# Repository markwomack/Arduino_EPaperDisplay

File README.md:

# Arduino EPaperDisplay Example
## Introduction
Arduino code to drive a Waveshare e-Paper display and example to demonstrate usage.

This code is written specifically for this e-Paper display model from Waveshare:

[2.13" Touch e-Paper HAT for Raspberry Pi, 250×122, Black / White, SPI](https://www.waveshare.com/product/displays/e-paper/epaper-3/2.13inch-touch-e-paper-hat.htm)

While this display is meant for use with a Raspberry Pi, it is still
compatible with Arduino. And in fact, Waveshare has Arduino example code to drive
the display (but not the touch screen) located here:

[epd2in13_V3](https://github.com/waveshare/e-Paper/tree/master/Arduino/epd2in13_V3)

I started with that Waveshare code to create my code. Much of the structure
and code is the same, just cleaned up with better class organization and added
features. I don't have any documentation about the SPI commands, so I have just copied
them over as-is. I will add more comments and documentation as I learn more.

## Licenses
All of this code is released under the MIT license except where noted in any files. The
original Waveshare code that was heavily used as a working example for this code had
it's own permissive license, which is noted in the file LICENSE-Waveshare. The fonts
used in this demo come from STMicroelectronics, and were originally included in the
Waveshare demo code. They have their own permissive license included in those files.

## Usage

### EPaperDisplay
EPaperDisplay is the class that defines the features and functions of the display. You will
typically create an instance at the start of the program, configure it for usage, and then
start the display for rendering.

#### Configuration
There are two main methods used to configure the display before usage. Typically you will
call these methods once before calling the start method.

- **setPinsAndSPI** - This method is called to configure the physical pins that the display
is connected to on the microcontroller (Arduino). The display uses the SPI protocol to
receive commands and data. The connections on the physical display are made either to
the solder points on the display or through the 40 pin Raspberry Pi header. The Pi
connections are documented in the picture below.

- **setDisplayOrientation** - This method sets the orientation of the display, effectively
where the origin of the screen is when rendering. Once the display has been started, the
orientation cannot be changed. The default orientation is ROTATE_0, so if that matches
your usage, then no call is necessary. The picture below shows the origins of each
orientation.

#### Using the Display

- **start** - The start method is called to initialize the display for usage. It returns a
PaintBuffer instance, which is used to render pixels, lines, rectangles, circles, fonts,
and bitmaps into the buffer for the display. More information on the
[PaintBuffer class](#paintbuffer) is below.
By default the display is created with an underlying buffer that is the full size of the
screen (FULL_BUFFER). For a black and white image at 122 x 250 pixels this is 4000 bytes.
If that is too much for your available runtime memory, you can pass the value
PARTIAL_BUFFER as a parameter to the start method and a smaller buffer will be created.
However, this has implications for rendering, which is discussed further in the [Demo Code
section](#demo-code) below. Typically you only need to call this method once, at the start
of the program, using a full size buffer.
- **stop** - The stop method is called to stop the display and release all of the memory
associated with it, this includes the underlying buffer and the associated PaintBuffer
object. After calling stop, the PaintBuffer instance returned from the call to the start
method should be discarded (it's already been freed in stop). Typically the stop method
is never called, but if there is a project that requires it, the display can be restarted
once again by another call to the start method.
- **setMode** - The setMode method must be called before the refresh method is called. It
'wakes' the display up from sleep mode and readys the display to receive data.
- **refresh** - The refresh method is used to render the current contents of the underlying
buffer to the display. If using a full size buffer (FULL_BUFFER), refresh only
needs to be called once to render the buffer to the display. If a partial buffer is used,
then 5 calls to refresh are required to render a full size buffer to the display. This is
discussed more in the [Demo Code section](#demo-code) below.
- **sleep** - After updating the display with the image data, you can call the sleep method
to place the display into low power sleep mode. In this mode the display will draw a 
very small amount of current, but the current image on the display will be maintained.
Once in sleep mode, use the setMode method to 'wake up' the display for rendering.
- **reset** - The reset method will perform a hardware reset of the display. This can be
used if the display becomes unresponsive.
- **getWidth** - This method returns the width of the display based on the current display
orientation. If the orientation is ROTATE_0 or ROTATE_180, the width will be 122, and
if the orientation is ROTATE_90 or ROTATE_270, the width will be 250.
- **getHeight** - This method returns the height of the display based on the current display
orientation. If the orientation is ROTATE_0 or ROTATE_180, the height will be 250, and
if the orientation is ROTATE_90 or ROTATE_270, the height will be 122.

#### Memory usage
The underlying buffer and PaintBuffer object are allocated with the call to the start method
and deallocated with the call to stop method. Typical usage has just the call to the start
method, so memory is not constantly allocated and deallocated. As mentioned above, by default
the EPaperDisplay class will allocated a buffer to match the full size of the display, which
is 122 x 250 black or white pixesl. It works out to 4000 bytes for the buffer.

### PaintBuffer
The PaintBuffer class has basic primitives to render points, lines, rectangles, circles, 
strings, and bitmaps. It uses the same underlying buffer created by the EPaperDisplay instance,
so memory is conserved. You get a reference to the paint buffer by calling the start method
of the display.

- **eraseBuffer** - Use eraseBuffer to clear the entire buffer to the given color. By default
this color is WHITE, but you can pass in BLACK as the value to set the entire buffer to black.
- **setColor** - Use the setColor method to set the color that elements will be drawn in. By
default this color is BLACK, but you can set the color to WHITE if drawing on a black
background. You can draw in inverse (BLACK background, WHITE drawings), then use the
eraseBuffer(BLACK) to fill the entire buffer with black, and use setColor(WHITE)
to change the drawing color, and render your desired objects.
- **getColor** - Returns the current color set in the PaintBuffer.
- **drawPixel** - Draws a pixel at the given point, in the current color.
- **drawLine** - Draws a line between two given points, in the current color.
- **drawRectangle** - Draws a rectangle between two given points, in the current color.
- **drawFilledRectangle** - Draws a filled rectangle between to given points, in the current
color.
- **drawCircle** - Draws a circle centered on a given point with the given radious, in the
current color.
- **drawFilledCircle** - Draws a filledcircle centered on a given point with the given radious,
in the current color.
- **drawBitmap** - Draws a bitmap, located in normal memory, of a given width and height with
the top left of the bitmap starting at a given point. Be default only the bits in the image
that are set will be rendered in the current color (skipUnsetBits = true). But if skipUnsetBits
parameter is set to false, then the set bits are rendered in the current color and the unset
bits are rendered in the opposite color.
- **drawBitmapFromProgMem** - Draws a bitmap, located in PROG_MEM, of a given width and height
with the top left of the bitmap starting at a given point. Be default only the bits in the image
that are set will be rendered in the current color (skipUnsetBits = true). But if skipUnsetBits
parameter is set to false, then the set bits are rendered in the current color and the unset
bits are rendered in the opposite color.
- **drawStringAt** - Draws a given string, using one of the built-in fonts located in PROG_MEM,
justified around a given point. If LEFT_JUSTIFIED, the default, the top/left of the string
will start at the given point. If CENTER_JUSTIFIED, the string will render to the left of the
point with the point being at the center/top of the rendered string. If RIGHT_JUSTIFIED, the
top/right of the string will end at the given point.
- **getWidth** - This method returns the width of the display based on the current display
orientation and buffer type. If the buffer type is FULL_BUFFER and the orientation is
ROTATE_0 or ROTATE_180, the width will be 122, and if the orientation is ROTATE_90 or
ROTATE_270, the width will be 250. If the buffer type is PARTIAL_BUFFER, then the buffer
is smaller, only 1/5th the size. If the orientation is ROTATE_0 or ROTATE_180, the width will
be 122, and if the orientation is ROTATE_90 or ROTATE_270, the width will be 50.
- **getHeight**- This method returns the height of the display based on the current display
orientation and buffer type. If the buffer type is FULL_BUFFER and the orientation is
ROTATE_0 or ROTATE_180, the height will be 250, and if the orientation is ROTATE_90 or
ROTATE_270, the height will be 122. If the buffer type is PARTIAL_BUFFER, then the buffer
is smaller, only 1/5th the size. If the orientation is ROTATE_0 or ROTATE_180, the width will
be 50, and if the orientation is ROTATE_90 or ROTATE_270, the width will be 122.
- **useOffsetStep** - If using a PARTIAL_BUFFER, and you still want the drawing to be rendered
as if there is a full buffer, then set this value to true (the default is false). You will need
to draw the full image multiple times, and this is discussed further in the
[Demo Code section](#demo-code) below.
- **setOffsetStep** - Do not use this method. It is called by the parent EParentDisplay to
coordinate with the PaintBuffer when refreshing with a partial buffer.

#### Image Basics
If you are creating your own images to be displayed, please keep in mind some of these basic
facts. A single image byte represents 8 pixels, one bit for each pixel, with the most significant
bit being the leftmost pixel. As an example, an image that is 24 pixels wide and 24 pixels in
height, each row of the image will be 3 bytes wide, and there will be 24 rows. The total number
of bytes will be 3 x 24 = 72. But what if the width of the image is not a multiple of 8? If we
have an image that is 21 pixels wide and 21 pixels in height, how many bytes should each row be?
2 bytes is not enough bits (16 bits) and 3 bytes is more than is needed (24 bits).

In cases where the pixel width is not a multiple of 8, we round up the number of bytes. In this
case: 3 bytes. The extra bits are just ignored. But they are still accounted for in the memory
allocated for the image. An image 24 x 24 pixels and an image that is 21 x 24 pixels require the
same amount of memory, 72 bytes.

The formula to use when determining the 'byte' width of an image is:

```
if (pixelWidth % 8 == 0) { 
  byteWidth = pixelWidth / 8;       // pixel width is a multiple of 8
} else {
  byteWidth = (pixelWidth / 8) + 1; // pixel width is not a multiple of 8, add a byte for padding
}
```

## Demo Code
The demo code in the Arduino_EPaperDisplay.ino sketch demonstrates usage for almost all of the
methods outlined.

### fullBufferDemo
This method renders a number of screens that are shown in the display when
the image buffer matches the full size of the display. It demonstrates use of all the shape,
string, and bitmap methods, using different colors and different display orientations. Normal
usage will probably not require multiple calls to the start and stop methods, but changing
orientation in the demo requires it.

### partialBufferDemo
This method demonstrates the usage of the EPaperDisplay and PaintBuffer
objects when only a partial buffer is allocated. When PARTIAL_BUFFER is given as a parameter to
the start method, a buffer that is only 1/5th the size of the full display is allocated. The
size of the buffer in pixels is only 122 x 50. Using a partial buffer changes the behavior of the
refresh method. Where the display was updated with just one call to refresh, the display will not
update until there have been 5 calls to refresh, each call updating a segment of the display. All
of the updates won't be displayed until the fifth call.

The first two examples show how this works when the display orientation is the default ROTATE_0.
Each segment is rendered independent of each other, working progressively down the 250 pixel height
of the display. This might be useful, but not likely. The situation gets even worse when the
display orientation is changed, as the third example shows. The text is rotation and displayed
in each segment. The issue is that drawing in the PaintBuffer is being done in the buffer coordinates,
not the display coordinates.

But in order for the display coordinates to make sense across all 5 buffer segments, you will need
to call the useOffsetStep method. This configures the PaintBuffer to work with the parent
EPaperDisplay object to count the number of refresh calls and to offset the coordinates accordingly.
But in order for this to work you will need to draw the same buffer contents each of the 5 calls to
refresh. It is a lot of duplication, but it works perfectly. All of the following examples demonstrate
this by drawing the same buffer 5 times using display coordinates instead of buffer coordinates. This
technique works with all display orientations and all of the paint buffer drawing methods. Pixels that
would be rendered outside of the mapped buffer are ignored so that memory is not corrupted.

## Questions, Concerns, Bugs
If you have any questions or encounter bugs, [please report a new issue](https://github.com/markwomack/Arduino_EPaperDisplay/issues).
Please provide as much detail and sample code that you can.

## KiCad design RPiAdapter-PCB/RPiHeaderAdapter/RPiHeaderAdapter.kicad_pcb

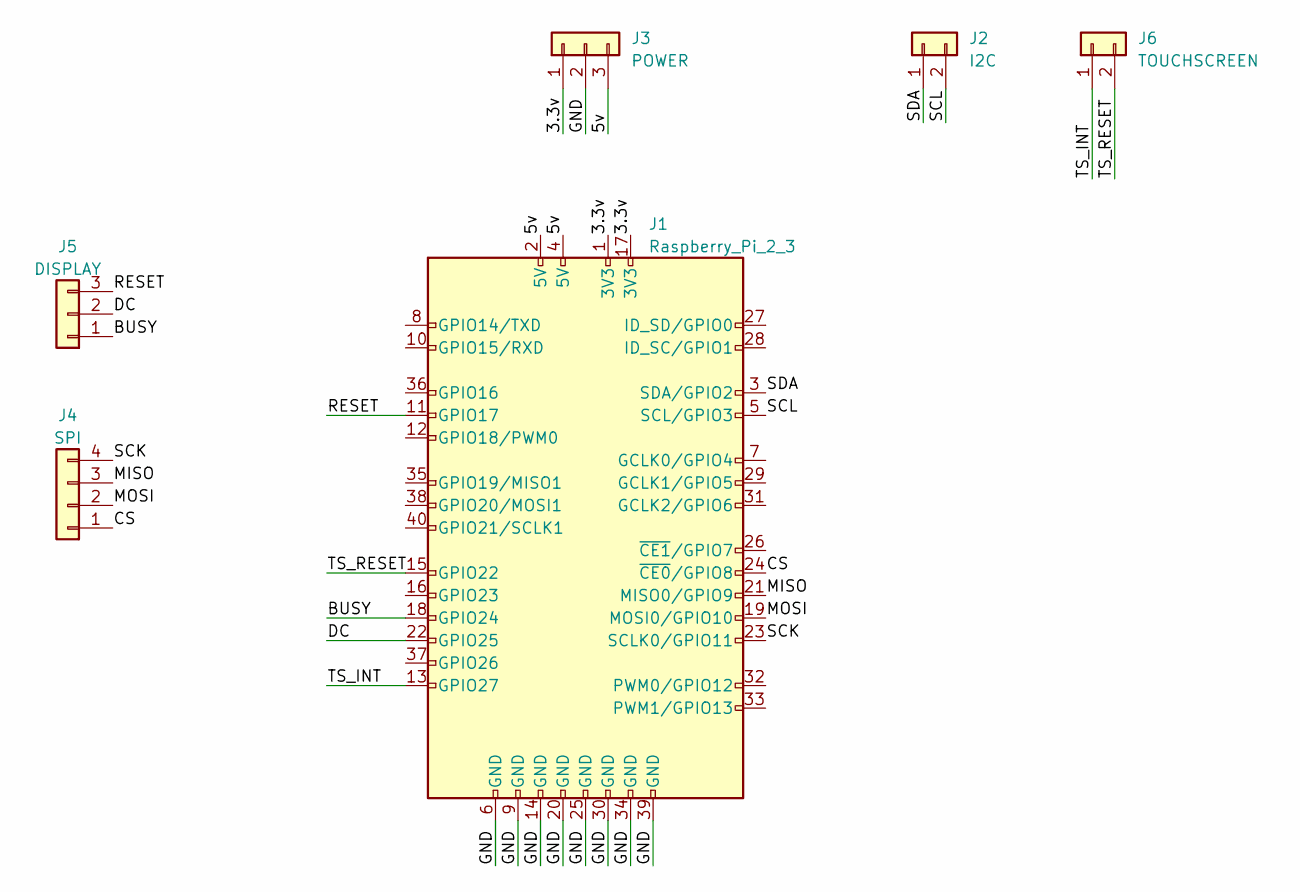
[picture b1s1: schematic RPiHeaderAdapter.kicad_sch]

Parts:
J1: Raspberry_Pi_2_3; PinHeader_2x20_P2.54mm_Vertical
J2: I2C; PinHeader_1x02_P2.54mm_Vertical
J3: POWER; PinHeader_1x03_P2.54mm_Vertical
J4: SPI; PinHeader_1x04_P2.54mm_Vertical
J5: DISPLAY; PinHeader_1x03_P2.54mm_Vertical
J6: TOUCHSCREEN; PinHeader_1x02_P2.54mm_Vertical

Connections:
/3.3v: J1.1 (3V3), J1.17 (3V3), J3.1
/5v: J1.2 (5V), J1.4 (5V), J3.3
/BUSY: J1.18 (GPIO24), J5.1
/CS: J1.24 (~CE0/GPIO8), J4.1
/DC: J1.22 (GPIO25), J5.2
/GND: J1.6 (GND), J1.9 (GND), J1.14 (GND), J1.20 (GND), J1.25 (GND), J1.30 (GND), J1.34 (GND), J1.39 (GND), J3.2
/MISO: J1.21 (MISO0/GPIO9), J4.3
/MOSI: J1.19 (MOSI0/GPIO10), J4.2
/RESET: J1.11 (GPIO17), J5.3
/SCK: J1.23 (SCLK0/GPIO11), J4.4
/SCL: J1.5 (SCL/GPIO3), J2.2
/SDA: J1.3 (SDA/GPIO2), J2.1
/TS_INT: J1.13 (GPIO27), J6.1
/TS_RESET: J1.15 (GPIO22), J6.2

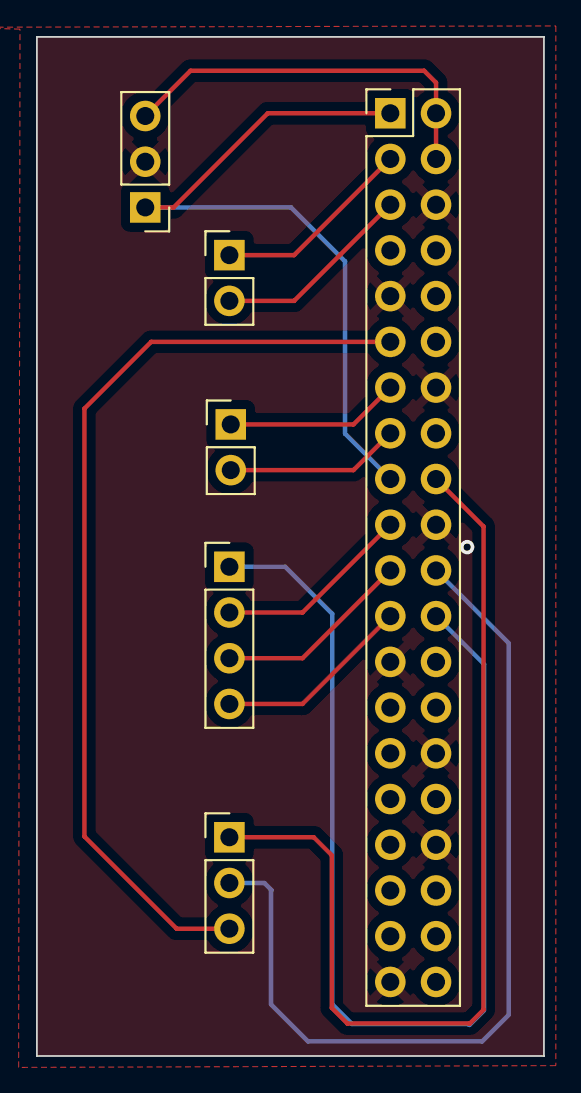
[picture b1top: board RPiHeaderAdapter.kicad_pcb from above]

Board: 2 copper layers, 28.2 x 56.6 mm, 6 parts (0 on the bottom side), 14 nets.

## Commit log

2023-04-20 Initial working version of everything except fonts
2023-04-20 Added image to show orientations
2023-04-20 Added image for RPi pins
2023-04-21 Feature set expanded to include bitmaps and fonts, as well as lots of other changes.
2023-04-21 Reorganization of data and doc files
2023-04-21 Support for partial buffer, more cleanup.
2023-04-21 Update RPi header pins used
2023-04-21 Changed DisplayRotation to DisplayOrientation
2023-04-21 Minor cosmetic changes
2023-04-22 Comment changes
2023-04-23 Start of touchscreen support, PCB for RPi header
